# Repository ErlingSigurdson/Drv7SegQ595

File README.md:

# Overview

**Drv7SegQ595** is a single-class Arduino library for driving a multiplexed 7-segment display using
a single 74HC595 shift register IC and a set of GPIO-driven transistors.

## Parent project

This library is a derivative (a fork) of the [Drv7Seg2x595](https://github.com/ErlingSigurdson/Drv7Seg2x595) library.
The main difference is that the parent project uses two daisy-chained 74HC595 shift register ICs, while this library
uses a single shift register IC and a set of 1 to 4 GPIO-driven transistors instead.

## Concept

7-segment displays are simple, cheap and reliable data output devices. However, interfacing them with
a microcontroller (MC) requires appropriate software and, most commonly, additional hardware.

Typically, 7-segment displays come in models with 1 to 4 character positions (digits). Number of input pins for
any given model equals 8 + number of positions, thus 9 is the minimum and 12 is the maximum (duplicated pins count
as one). Driving such a display requires a number of individual signals equal to the number of the input pins:
* 8 signals to turn ON and OFF individual segments (including a dot segment, also known as a decimal point or DP).
* 1 to 4 signals to turn ON and OFF whole positions.

Due to significant number of required signals, output-extending devices, such as output shift registers, are commonly
used. **74HC595**, sometimes simply called **595**, is a widely used 8-bit serial-in, parallel-out (SIPO) shift register
integrated circuit (IC) commonly employed to drive 7-segment displays. A single 595 provides an 8-bit shift register,
which is sufficient to hold a segment pattern corresponding to a glyph. The register's 8 bits are referred to as
**segment byte** or **`seg_byte`**.

Another 1 to 4 signals come from a set of GPIO-driven transistors. Combined with the shift register, it is sufficient
for controlling any typical 7-segment display.

The API provided by this library allows for control over 1 to 4 character positions. The number of ns to be
used must be specified during the driver configuration.

## Multiplexing

This library relies on **multiplexing**: a way of driving a multi-digit 7-segment display by turning on only one
character position at a time in quick succession, in a cycle. Because the multiplexing cycle runs faster than
the eye can follow, all positions appear to be lit continuously, even though only one is actually turned on at
any given moment.

This approach greatly simplifies the circuit because it doesn't rely on a separate set of segment-control outputs
for every position and instead utilizes the single set of segment-control outputs shared by **all** positions
(the defined segment pattern shows up only on the intended position anyway, because only that position will be
turned on at the appropriate moment).

### Ghosting and countermeasures

Advantages of multiplexing come with an unwanted side effect called **ghosting**: segments can seem to have a faint,
"ghost-like" glow on positions that are supposed to be off. To avoid this effect, the library utilizes the anti-ghosting
techniques that involve retention of a currently output glyph on a respective position for a short period of time.
Duration of the said period can be fine-tuned by the library user via the library's API.

The library's anti-ghosting logic is based on a non-blocking, `micros()`-based timer. No blocking, `delay()`-based
timers are used.

## Position switching

Every character position is turned on (powered) by setting the output level of a GPIO specified during the driver
configuration either to high or low, because it makes it possible to source/sink current from/to that pin and thus
to drive a switching device, such as a transistor.

Depending on the display type (whether it's a common-cathode or a common-anode device) and the switching device type
(whether it's an active-high device, like an NPN BJT or an N-channel MOSFET, or an active-low device, like a PNP BJT or
a P-channel MOSFET), positions will be turned on either by high or low digital output level. The API provided by this
library supports both variants. The switching type (active-high or active-low) must be specified during the driver
configuration.

## Data transfer (shifting)

The driver implemented by this library uses either bit-banging or SPI for shifting the data into the shift register.
If you choose bit-banging, the driver will use whatever GPIO pins you assign to it. If you choose SPI, the driver will
use the default SPI instance (although support for non-default and multiple SPI instances may be added later).

## Reference schematic

Here's a typical circuit diagram for the described arrangement (assumes a common-cathode display):

.png)

For convenience, the example sketch default constant values corresponds to the circuit diagram provided here.

Wiring for a common-anode display is almost identical, the only difference being that the transistors' emitters
should connect to the display's common pins and their collectors should connect to the circuit's positive rail (VCC).

The wiring in your circuit **may** differ from the provided schematic to some degree, and the library will still be
applicable as long as your circuit complies with the premise of the `seg_byte` and the position-control pins' distinct
roles.

### Notes on the reference schematic

* Power your 595 with the same voltage your MC runs on.
* Transistors Q1..Q4 are intended to be general-purpose NPN BJTs such as MMBT3904 (assumed by the reference PCB design,
see below), 2N3904, 2N4401, 2N2222, or BC548. You can even use a [KT315](https://ru.wikipedia.org/wiki/%D0%9A%D0%A2315),
comrade.
* If the display segment LEDs are too bright, or if you notice visible brightness changes when the DP blinks, increase
the R0..R7 resistor values to around 470-680 Ω. This is especially advisable if your 595 is powered from a 5 V supply.

## API usage

Include the library:
```cpp
#include <Drv7SegQ595.h>    // Arduino style.
//#include "Drv7SegQ595.h"  // Generic embedded programming style.
```

### Driver configuration

Choose **one** of the following variants.

Bit-banging:
```cpp
// Prototype.
int32_t begin_bb(PosSwitchType pos_switch_type,  // Whether high or low output level turns on a character position.
                 uint32_t data_pin,              // The pin that outputs the next bit value to be shifted.
                 uint32_t latch_pin,             // The pin that propagates the shifted data to the output register.
                 uint32_t clock_pin,             // The pin that commands the next bit value to be shifted.
                 int32_t pos_1_pin,              // Number of the MC pin that will control the 1st position.
                 int32_t pos_2_pin,              // Number of the MC pin that will control the 2nd position.
                 int32_t pos_3_pin,              // Number of the MC pin that will control the 3rd position.
                 int32_t pos_4_pin               // Number of the MC pin that will control the 4th position.
                );

// Example call.
Drv7Seg.begin_bb(Drv7SegActiveHigh,  // Other option is Drv7SegActiveLow.

                 /* Digital output pins you want to use for shifting the data into the IC.
                  * Pin numbers must correspond to the pin numbering specified
                  * by the Arduino core you're using.
                  */
                 6, 7, 8,

                 /* Digital output pins you want to use for character position switching.
                  * Pin numbers must correspond to the pin numbering specified
                  * by the Arduino core you're using.
                  *
                  * The first one of these arguments (1st position-control pin) is required.
                  * Subsequent arguments are optional.
                  * The driver will be configured to control the number of positions
                  * equal to the number of arguments that weren't omitted.
                  */
                 10,  // This parameter is required.
                 11,  // This parameter is optional.
                 12,  // This parameter is optional.
                 9    // This parameter is optional.
                );
```

SPI with default pins:
```cpp
/* Mostly identical to the bit-banging variant, but among the shifting pins only the latch pin needs to be specified
 * (the default MOSI pin must be used as a data pin and the default SCK pin must be used as a clock pin).
 */

// Example call.
Drv7Seg.begin_spi(...
                  LATCH_PIN,
                  ...
                 );
```

SPI with custom pins:
```cpp
/* Mostly identical to the bit-banging variant, but the data pin role goes to
 * the specified MOSI pin and the clock pin role goes to the specified SCK pin.
 */

// Example call.
Drv7Seg.begin_spi_custom_pins(...
                              MOSI_PIN,
                              LATCH_PIN,
                              SCK_PIN,
                              ...
                             );
```

### Status check

Get the driver configuration status (check if it was configured successfully):
```cpp
int32_t drv_config_status = Drv7Seg.get_status();
// Loop the error output if the driver configuration was unsuccessful.
if (drv_config_status < 0) {  // If an error is detected.
    while(true) {
        Serial.print("Error: driver configuration failed, error code ");
        Serial.println(drv_config_status);
        delay(INTERVAL);
    }
}
```
You can also check the value returned by `begin_*()` instead of calling `get_status()`.

### Output

Assign the glyphs you want to output to each character position:
```cpp
// Prototype.
int32_t set_glyph_to_pos(uint8_t seg_byte,  // A byte that corresponds to the glyph to be output.
                         Pos pos            // A number of the position the glyph must be output on.
                        );

// Example call (single).
Drv7Seg.set_glyph_to_pos(
                         0b00010001,  // Depending on wiring, may represent character '1'.

                         /* Valid arguments are Drv7SegPosN, where
                          * N => 1
                          * and
                          * N <= the number of positions the driver was configured to use.
                          */
                          Drv7SegPos1
                        );

/* Example calls (typical implementation).
 *
 * Make recurrent calls in quick succession for all positions your driver was configured to use.
 */
Drv7Seg.set_glyph_to_pos(seg_byte_minutes_tens, Drv7SegPos1);
Drv7Seg.set_glyph_to_pos(seg_byte_minutes_ones, Drv7SegPos2);
Drv7Seg.set_glyph_to_pos(seg_byte_seconds_tens, Drv7SegPos3);
Drv7Seg.set_glyph_to_pos(seg_byte_seconds_ones, Drv7SegPos4);
```

Commence the actual output:
```cpp
// Call it inside the loop() function.
Drv7Seg.output_all();
```

If you want a more fine-grained control over output, you can use a lower level method.
Using it will override the glyph assignment done with `set_glyph_to_pos()` calls.
```cpp
// Prototype.
int32_t output(uint8_t seg_byte,  // A byte that corresponds to the glyph to be output.
               Pos pos            // A number of the position the glyph must be output on.
              );

// Example call (single).
Drv7Seg.output(
               0b00010001,  // Depending on wiring, may represent character '1'.

               /* Valid arguments are Drv7SegPosN, where
                * N => 1
                * and
                * N <= the number of positions the driver was configured to use.
                */
               Drv7SegPos1,
              );

/* Example calls (typical implementation).
 *
 * Make recurrent calls in quick succession for all positions your driver was configured to use.
 */
Drv7Seg.output(seg_byte_minutes_tens, Drv7SegPos1);
Drv7Seg.output(seg_byte_minutes_ones, Drv7SegPos2);
Drv7Seg.output(seg_byte_seconds_tens, Drv7SegPos3);
Drv7Seg.output(seg_byte_seconds_ones, Drv7SegPos4);
```

### Anti-ghosting

Ghosting prevention involves retention of a currently displayed glyph on a corresponding position for a short period
of time. The duration of such period has a reasonable default of 600 microseconds, but you can override it.
```cpp
/* If you encounter ghosting, random flickering, or glyphs appear too dim or show inconsistent brightness,
 * try passing a higher value (about 1000 to 4000).
 * If you encounter constant flickering, try passing a lower value (about 10 to 400).
 */
Drv7Seg.set_anti_ghosting_retention_duration(1000);
```

Refer to `Drv7SegQ595.h` for more API details.

## Special cases

* **Multiple drivers**. You can create additional instances of `Drv7SegQ595Class` and use them for driving multiple
displays, but you shouldn't employ SPI by more than one instance at a time.

* **Single-digit displays**. With a single-position display there's usually no purpose in a switchable signal that
turns the only character position ON and OFF (all control job can be done by `seg_byte` alone), nor there's a need for
multiplexing. Still, you can use this library to control a single-digit display in a pinch. You can either:
    - assign a single position-control pin during the driver configuration and use that pin to control your only
position (in this case the multiplexing logic will still be applied, but the single position will always be the one
to be turned on next);
    - ignore the position-control pins completely and power your display directly by connecting it to GND or VCC,
according to the display type. You will still have to pass a single position-control pin argument during the driver
configuration to comply with the library logic, but its particular value becomes mostly irrelevant (pick any GPIO
pin available for driving).

* **Ignoring certain digits**. If you, for instance, have a 4-position display and for some reason you want to use
only positions 2 and 3, it's completely OK, you can do that using this library. Pass two position-control pins during
the driver configuration: one for the 2nd physical position (it'll correspond to `Drv7SegPos1` within the library logic)
and another one for the 3rd physical position (it'll correspond to `Drv7SegPos2` within the library logic).

## Dependencies

* `SPI.h` library implementation for the Arduino core and the board (device) you're using.
It is available for most major Arduino cores, although it isn't guaranteed that every single Arduino core in the world
will have it as well. In an unlikely case when it is not implemented for your Arduino core or device, you can still use
this library's bit-banging mode, but in order to avoid compilation errors you'll have to manually comment out the
`#define DRV7SEGQ595_SPI_PROVIDED_ASSUMED` preprocessor directive in `Drv7SegQ595.h`.

* **SegMap595** library (available from Arduino Library Manager, also see links below) is used in the example sketch
in order to simplify byte mapping, but aside from that it's not a prerequisite for using `Drv7SegQ595.h`.

## Compatibility

The library works with any Arduino-compatible MC capable of bit-banging or SPI data transfer.

Availability of the configuration variant that takes custom-assigned SPI pins relies on the capabilities of a given MC
and the corresponding `SPI.h` implementation. As of the last update to this library, this variant is only available for
ESP32 and STM32 MC families.

### Rich circuit diagram

This library includes a [KiCAD](https://www.kicad.org/) [project](extras/kicad/) that provides a reference schematic.
PCB layout is not included though. The project was created in KiCAD 9.0.

## To-do list

* Add support for using non-default and multiple SPI instances.

## Licensing

* The software part of this library, as well as its documentation, is licensed under the **MIT License**
(see `LICENSE` [here](LICENSE)).
* All hardware-related files in this library, including illustrations, are licensed under the **CERN-OHL-P v2**
(see `extras/kicad/LICENSE_HARDWARE` [here](extras/kicad/LICENSE_HARDWARE)).

## Links

### This library
* [Primary repository on GitHub](https://github.com/ErlingSigurdson/Drv7SegQ595)
* [Backup repository on GitFlic](https://gitflic.ru/project/efimov-d-v/drv7segq595)
* [Backup repository on Codeberg](https://codeberg.org/ErlingSigurdson/Drv7SegQ595)

### SegMap595
* [Primary repository on GitHub](https://github.com/ErlingSigurdson/SegMap595)
* [Backup repository on GitFlic](https://gitflic.ru/project/efimov-d-v/segmap595)
* [Backup repository on Codeberg](https://codeberg.org/ErlingSigurdson/SegMap595)

### Drv7Seg2x595
The parent project of this library. Uses a second shift register IC instead of a set of GPIO-driven transistors.
* [Primary repository on GitHub](https://github.com/ErlingSigurdson/Drv7Seg2x595)
* [Backup repository on GitFlic](https://gitflic.ru/project/efimov-d-v/drv7seg2x595)
* [Backup repository on Codeberg](https://codeberg.org/ErlingSigurdson/Drv7Seg2x595)

## Contact details

**Maintainer** — Dmitriy Efimov aka Erling Sigurdson
* <efimov-d-v@yandex.ru>
* <erlingsigurdson1@gmail.com>
* Telegram: @erlingsigurdson

Your feedback and pull requests are welcome.

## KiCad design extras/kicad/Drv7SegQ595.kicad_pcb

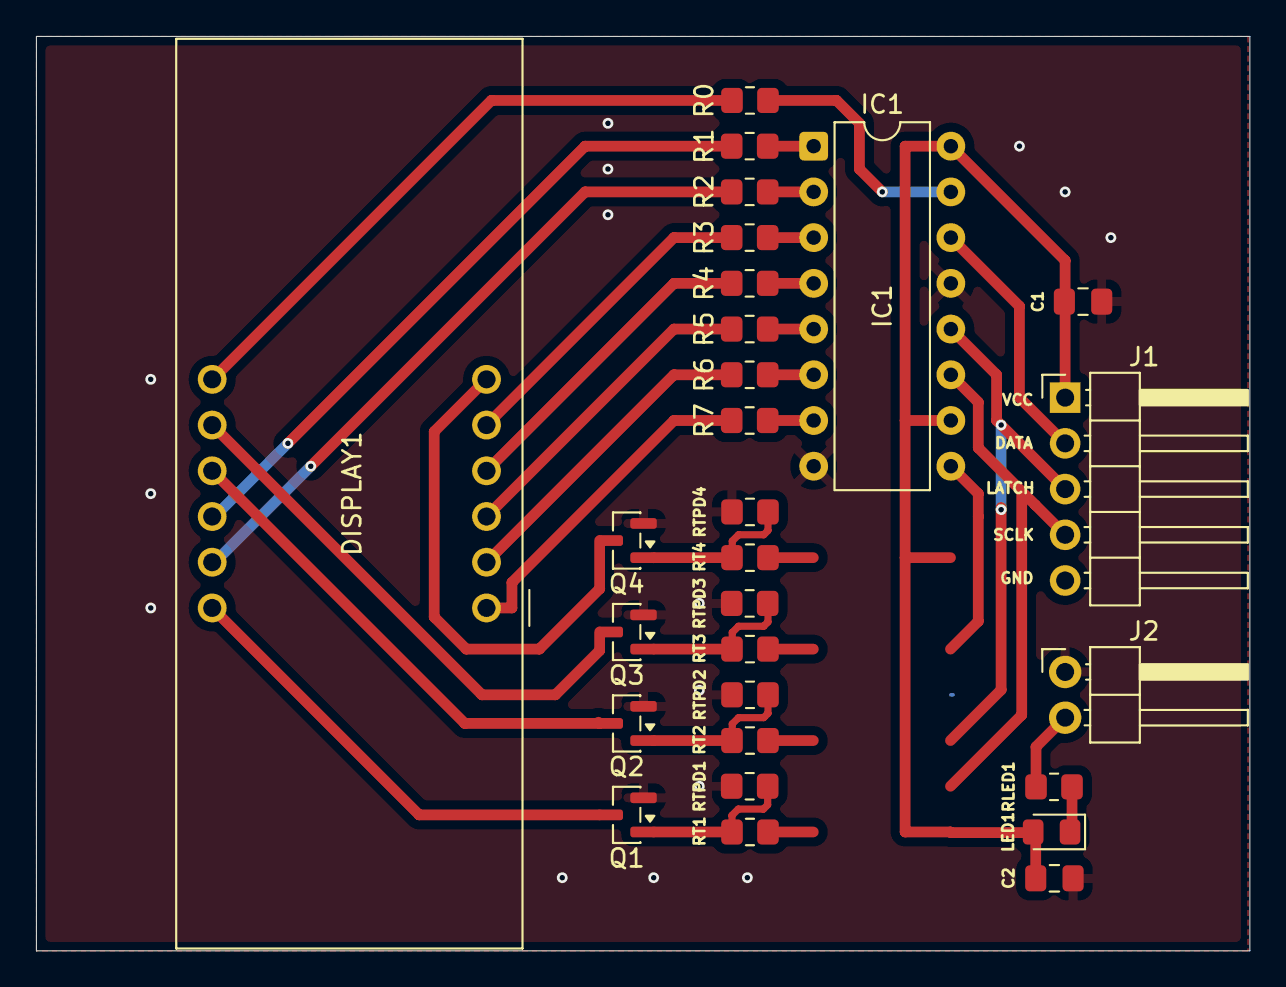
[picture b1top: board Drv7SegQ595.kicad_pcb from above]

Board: 2 copper layers, 67.4 x 50.8 mm, 28 parts (0 on the bottom side), 32 nets.

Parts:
C1, C2: 0.1 μF; C_0805_2012Metric_Pad1.18x1.45mm_HandSolder
D1: LED1; LED_0805_2012Metric_Pad1.15x1.40mm_HandSolder
DISPLAY1: display_7seg_4d; display_7seg_4d_0.56in
IC1: 74HC595; DIP-16_W7.62mm
J1: INTERFACE; PinHeader_1x05_P2.54mm_Horizontal
J2: PWR_LED_JMP; PinHeader_1x02_P2.54mm_Horizontal
Q1, Q2, Q3, Q4: MMBT3904; SOT-23
R0, R1, R2, R3, R4, R5, R6, R7: 330; R_0805_2012Metric_Pad1.20x1.40mm_HandSolder
RLED1: 680; R_0805_2012Metric_Pad1.20x1.40mm_HandSolder
RT1, RT2, RT3, RT4: 1k5; R_0805_2012Metric_Pad1.20x1.40mm_HandSolder
RTPD1, RTPD2, RTPD3, RTPD4: 47k; R_0805_2012Metric_Pad1.20x1.40mm_HandSolder

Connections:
GND: C1.2, C2.1, IC1.8 (GND), IC1.13 (~OE), J2.2, Q1.2 (E), Q2.2 (E), Q3.2 (E), Q4.2 (E), RTPD1.1, RTPD2.1, RTPD3.1, RTPD4.1
unnamed: D1.1 (K), RLED1.2
unnamed: DISPLAY1.11 (A), R2.1
unnamed: DISPLAY1.7 (B), R0.1
unnamed: DISPLAY1.4 (C), R4.1
unnamed: DISPLAY1.12 (D1), Q1.3 (C)
unnamed: DISPLAY1.9 (D2), Q2.3 (C)
unnamed: DISPLAY1.8 (D3), Q3.3 (C)
unnamed: DISPLAY1.6 (D4), Q4.3 (C)
unnamed: DISPLAY1.2 (D), R6.1
unnamed: DISPLAY1.3 (DP), R5.1
unnamed: DISPLAY1.1 (E), R7.1
unnamed: DISPLAY1.10 (F), R1.1
unnamed: DISPLAY1.5 (G), R3.1
unnamed: IC1.14 (DATA), J1.2 (DATA/MOSI)
unnamed: IC1.12 (LATCH), J1.3 (LATCH)
unnamed: IC1.15 (Q0), R0.2
unnamed: IC1.1 (Q1), R1.2
unnamed: IC1.2 (Q2), R2.2
unnamed: IC1.3 (Q3), R3.2
unnamed: IC1.4 (Q4), R4.2
unnamed: IC1.5 (Q5), R5.2
unnamed: IC1.6 (Q6), R6.2
unnamed: IC1.7 (Q7), R7.2
unnamed: IC1.11 (SCLK), J1.4 (SCLK/SCK)
unnamed: J1.5 (D4), RT4.2
unnamed: J2.1, RLED1.1
unnamed: Q1.1 (B), RT1.1, RTPD1.2
unnamed: Q2.1 (B), RT2.1, RTPD2.2
unnamed: Q3.1 (B), RT3.1, RTPD3.2
unnamed: Q4.1 (B), RT4.1, RTPD4.2
VCC: C1.1, C2.2, D1.2 (A), IC1.10 (RST), IC1.16 (VCC), J1.1 (VCC)

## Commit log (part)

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2025-10-26 Work in progress. Basic API works now.
2025-10-26 Work in progress.
2025-10-29 Update README.
2025-10-29 Add switch polarity (re NPN/PNP N-channel/P-channel) as a third parameter for init.
2025-10-30 Update API description.
2025-10-30 Update example sketch.
2025-10-30 Work further on implementation and API.
2025-10-30 Fix typo.
2025-11-05 Fix typo re library name (was 585, now 595).
2025-11-09 Update README re compatibility and dependencies.
2025-11-09 1) Add guards related to SPI.h not being implemented, 2) Change class and singleton object name to match Arduino convention.
2025-11-09 Update README re links.
2025-11-09 Update README re list style.
2025-11-09 Update README re dependency on SegMap595.
2025-11-10 Add non-delay()-based non-blocking timer.
2025-11-10 Fix default anti-ghosting pause value.
2025-11-10 Add macro for default anti-ghosting pause.
2025-11-10 Misc.
2025-11-11 Update anti-ghosting retention logic.
2025-11-11 Slightly update anti-ghosting retention code logic.
2025-11-11 Minor comment update.
2025-11-11 Add parameter enums.
2025-11-12 Add file descriptions.
2025-11-12 Fix example sketch error + minor comment and description updates.
2025-11-12 Update counter in example sketch.
2025-11-12 Clean old notes from header file.
2025-11-12 Remove mention of additional driver object.
2025-11-13 In progress.
2025-11-13 Update example sketch: add macro for max count.
2025-11-15 HUGE update.
2025-11-15 Make blanking sequence send two bytes instead of one to prevent visial artefacts being displaye.
2025-11-15 Update example sketch notes re dot segment blinking.
2025-11-15 Update implementation: update macros (return codes), update enum parameters inner check in methods.
2025-11-16 Update implementation.
2025-11-16 Update library version in library.properties (lower it under 1.0.0).
2025-11-16 Add notes to README.
2025-11-16 Fix timer value variables (from 64 to 32 bit).
2025-11-16 Add early return to timer if retention duration is zero.
2025-11-16 Lower default anti-ghosting retention duration.
2025-11-16 Change default anti-ghosting retention duration.
2025-11-16 Update custom SPI pins defaults.
2025-11-17 Minor update: int32_t to uint32_t in begin_helper().
2025-11-17 Major polish.
2025-11-17 Update comments on what decimal point is.
2025-11-17 Add tiny nits on wording.
2025-11-17 Add tiny nits on single quotes usage.
2025-11-18 Update wording.
2025-11-18 Update implementation and header re comments contents and output() return codes + add TODO to README
2025-11-18 Update wording (light up -> turned on).
2025-11-18 Update default custom MOSI pin in the example sketch.
2025-11-18 Minor doc update in header file.
2025-11-18 Update comments in implementation file.
2025-11-18 Fill out keywords.txt.
2025-11-18 Introduce position bits duplication check.
2025-11-18 Fix typo (add missing parentheses after `if`).
2025-11-19 Fix bug related to pos bit duplication prevention.
2025-11-19 Simplify anti-ghosting retention logic, move previous_micros update to the end of output() method.
2025-11-19 Update README re TODO re description on how to call output().
2025-11-19 Add _active_positions reset on every begin_*() method call.
2025-11-19 Update files' cross-reference description.
2025-11-19 Change example sketch file name.
2025-11-20 Make anti_ghosting_next_pos_to_output() return valid results even if non-neighboring character positions where marked as active.
2025-11-20 Pack position bits into array to use within logic that indicates next position to be turned on after anti-ghosting retention.
2025-11-21 Add comments on next available position detection logic.
2025-11-22 Provide reset of variables related to anti-ghosting logic on driver (re)configuration.
2025-11-25 Introduce get_status() method, update example sketch appropriately.
2025-11-28 Revert "Change example sketch file name."
    This reverts commit 266406bd742dd369a88eabd63a603ba59cb2e28b.
2025-11-28 Update comments on anti_ghosting_next_pos_to_output().
2025-11-28 Update comments on the reset of variables related to anti-ghosting logic.
2025-11-28 Add return description to private methods.
2025-11-28 Update API comment.
2025-11-28 Add comment on less than 4 character positions in example sketch.
2025-11-28 Update comments in example sketch.
2025-11-28 Create separate directories for images and KiCad files within 'assets' directory, but this time add placeholder.
2025-11-29 Fix comment on anti_ghosting_next_pos_to_output().
2025-11-29 1) Change pin number type (int32_t -> uint32_t), 2) Fix initialization of position bits array, 3) Update relevant comments.
2025-11-29 Add paragraph to library.properties (duplicate of sentence).
2025-11-29 Update README (in progress, finally started writing proper API usage description).
2025-11-30 Update output() description in README.
2025-11-30 Update README on configuration variants.
2025-11-30 Update README re misc.
2025-11-30 Change directory name from assets to extras in order to comply with Arduino library specification (https://arduino.github.io/arduino-cli/1.3/library-specification/)
2025-12-01 Add KiCAD files.
2025-12-01 Paste more clear text of CERN-OHL-P v2.
2025-12-01 Add note file to 'extras' directory.
2025-12-01 Update note on extras directory.
2025-12-01 Add note on compatibility in regard to custom SPI pins.
2025-12-01 Update README (major additions).
2025-12-01 1) Move DISPLAY1 reference to F.Silkscreen, 2) Move main header notes (place them in even row).
2025-12-01 1) Fix headers' and ICs' warnings on difference between ad hoc footprints and library, 2) Fix copper zones, 3) Add more informative header pins' text to silkscreen.
2025-12-01 Create gitignore, add rule to ignore KiCAD's cache files.
2025-12-01 Update image from KiCAD 3D viewer.
2025-12-01 Fix typos in README.
2025-12-01 Update README (generic spacing, some wording).
2025-12-02 Update README: fix typo.
2025-12-02 Update comment on __has_include() macro.
2025-12-02 Add cosmetic updates to main header file.
2025-12-02 Change position bit argument placement style in example sketch.
2025-12-02 Fix incidental removal of default anti-ghosting retention duration macro value.
2025-12-02 Update comments in source files.
2025-12-02 Update README re multiplexing.
2025-12-02 Update README re links syntax + add image with PCB 3D rendering.
2025-12-02 Fix link to image.
2025-12-02 Update links section in README.
2025-12-02 Update default anti-ghosting retention duration value referenced in README.
2025-12-03 Change PCB image size using HTML instead of basic markdown.
2025-12-03 Limit size of circuit diagram image using HTML.
2025-12-03 Add link to Codeberg remote repo.
2025-12-03 Fix image path.
2025-12-03 Make clickable link to full-size image remain below preview.
2025-12-03 Return circuit diagram image to basic markdown, add preview file.
2025-12-03 Change preview image size for circuit diagram.
2025-12-03 Try to resolve remote git repo services' mardown interpreter (README viewer) issues re images.
2025-12-03 Revert "Update PNG image of circuit diagram."
    This reverts commit d6b1fd503dc3f0356f78221437ddeea3e69f1220.
2025-12-03 Update README re clickability for full-size image.
2025-12-03 Update README re images.
2025-12-03 Revert "Update README re images."
    This reverts commit f34fc31b0ae07bd833b555a354ddc1f234492b84.
2025-12-03 Update README re link to full-size image text style.
2025-12-03 Update README (general description).
2025-12-03 Update README (general).
2025-12-04 Update README and documentation elsewhere.
2025-12-05 Update README and example sketch (close to version 1.0.0).
2025-12-05 Change 'License' to 'Licensing'.
2025-12-05 Update README re articles.
2025-12-05 Fix changed variable names in example sketch.
2025-12-05 Update library version in library.properties.
2025-12-05 Update README: list begin_bb() arguments more conveniently.
2025-12-05 Rotate thermal spokes at interface header pads and make them wider.
2025-12-05 Fix typo in README.
2025-12-05 Fix code syntax-related typos in README.
2025-12-05 Update README re anti-ghosting retention duration fine-tuning.
2025-12-05 Restrict custom SPI pin assignment to ESP32 only, reflect it in documentation.
2025-12-05 Edit comment style in README.
2025-12-05 Add comment on additional class instances.
2025-12-06 Make F.Cu (front copper) layer in KiCAD PCB design visible by default.
2025-12-06 Update README: change section name, change item order in list, fix list indentation.
2025-12-06 Introduce library's own shift_out() method to account for standard Arduino shiftOut() implementation flaw (lack of driving clockPin LOW before starting shift).
2025-12-07 Document shift_out() method.
2025-12-07 Introduce alternative output interface.
2025-12-08 Finish introducing new output interface.
2025-12-08 Update README: add minor note.
2025-12-08 1) Fix incorrect call example in README, 2) Update keywords.txt (BTW in had to be done by 1.1.0, but it wasn't).
2025-12-08 Revert "Restrict custom SPI pin assignment to ESP32 only, reflect it in documentation."
    This reverts commit 203a536042a8bb3db60ae50e36bafbc6d5fa1997.
2025-12-08 Update README re availability of custom SPI pin assignment for STM32 devices.
2025-12-09 Update README: add to-do list.
2025-12-09 Update README: add notes on data transfer (shifting) in general, on bit-banging and on SPI.
2025-12-09 Minor doc fix.
2025-12-09 Update README: add link to Drv7Seg2x595 (parent project).
2025-12-09 Tiny spacing correction in header file.
2025-12-09 Tiny spacing correction in cpp file.
2025-12-09 Introduce major rewrite, it compiles now.
2025-12-09 Make it working (first successful tests).
2025-12-10 Update general library description.
2025-12-10 Update README: order of links.
2025-12-10 Update documentation in header file.
2025-12-10 Fix naming in example sketch (_BIT to _PIN).
2025-12-10 Update cpp file.
2025-12-10 Update keywords.txt.
2025-12-10 Global update of macros names (DRV7SEG2X595 to DRV7SEGQ595)
2025-12-10 Minor spacing fix.
2025-12-14 Update BJT base resistors' value.
2025-12-14 Remove *kicad_prl file and add it to .gitignore.
2025-12-14 Reworking the KiCAD symbols.
2025-12-15 Major update of KiCAD files.
2025-12-15 Add .bak files to .gitignore.
2025-12-15 Add reference to KiCAD version to README.
2025-12-15 Update README: minor polish.
2025-12-15 Rearrange .gitignore a little bit.
2025-12-15 Rearrange mounting holes symbols in KiCAD schematic file.
2025-12-15 Update README: re wording re KiCAD version.
2025-12-15 Update images.
2025-12-15 Update circuit diagram (schematic) image.
2025-12-15 Update all images.
2025-12-15 Update symbol for transistors.
2025-12-15 Increase RLED1 value to 680 Ohm.
2025-12-15 Update README re consistency in hyphenation.
2025-12-16 Update README re overriding default anti-ghosting retention period.
2025-12-16 Bump BJT base pull-down resistors values to 47k.
2025-12-19 Add pinMode() call for position control bits.
2025-12-19 Code style fixes.
2025-12-20 1) Add validity check for position control pins 2-4 (in case they are < -1); 2) Clarify text delimiters.
2025-12-20 Fix pinMode() calls logic.
2025-12-20 Update library name in example sketch.
2025-12-20 Update README: rewriting for this derivative in progress.
2025-12-20 Rename all KiCAD files to correspond to this library's name.
2025-12-20 Update KiCAD files contents (mostly schematic) to match this library.
2025-12-20 Update README: gradual progress.
2025-12-20 Update schematic image file (get one from updated KiCAD project).
2025-12-22 Update default anti-ghosting retention duration value and relevant comments.
2025-12-22 Update library description in README and library.properties.
2025-12-22 Update README: recommended fixes.
2025-12-22 Add guard against turning on invalid position control pins.
2025-12-22 Update schematic (and corresponding image): move J2 symbol label upwards.
2025-12-25 Update docs.
2025-12-29 Update according to SegMap595 update + add preprocessor conditional for Serial.begin().

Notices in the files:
README.md:
(see `extras/kicad/LICENSE_HARDWARE` [here](extras/kicad/LICENSE_HARDWARE)).
extras/kicad/Drv7SegQ595.kicad_pcb:
Copyright (c) 2025 Dmitriy Efimov aka Erling Sigurdson
Licensed under CERN-OHL-P v2
